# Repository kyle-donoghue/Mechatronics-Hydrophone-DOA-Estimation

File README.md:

# Mechatronics-Hydrophone-DOA-Estimation
 My work with using passive hydrophones to estimate the direction of arrival of an underwater acoustic ping. This project was made for SDSU's Mechatronics team for deployment on an autonomous submarine competition.

# How It Works
2 passive Aquarius hydrophones are connected to an op-amp network for amplification that is conneected to an Analog Digilent Discovery 2. The ADD2 is used as an ADC with their provided SDK. Python is then used for real-time capturing and processing of hydrophone data using threaded workloads and queues to send data between the workloads. Data is captured at 500kS/s at 12-bits continuously with a 1 second buffer on the recording thread and then is sent to the processing thread.

The processing thread then uses a 127-order bandpass filter from 20k-40kHz. Then, an energy vs. time signal is made in that frequency spectrum to see where in the buffer the spike of the acoustic ping is. Once the spike is located, the first couple of periods of it is taken and used for direction-of-arrival estimation. Next, the STFT is taken of the signal and a new signal is made up of the peaks of every FT in the series. This new complex signal has all the data we need for DOA estimation due to its time relative information on phase differences of the two hydrophones.

Now, Burg's Maximum Entropy Method is used on this new complex signal to calculate the power at each possible degree to make a power vs. degree signal. Finally, the peaks of this signal are found and their indices in the array correspond to the DOA. Finally, the first peak's index is is sent out to the main computer for use in autonomous direction.

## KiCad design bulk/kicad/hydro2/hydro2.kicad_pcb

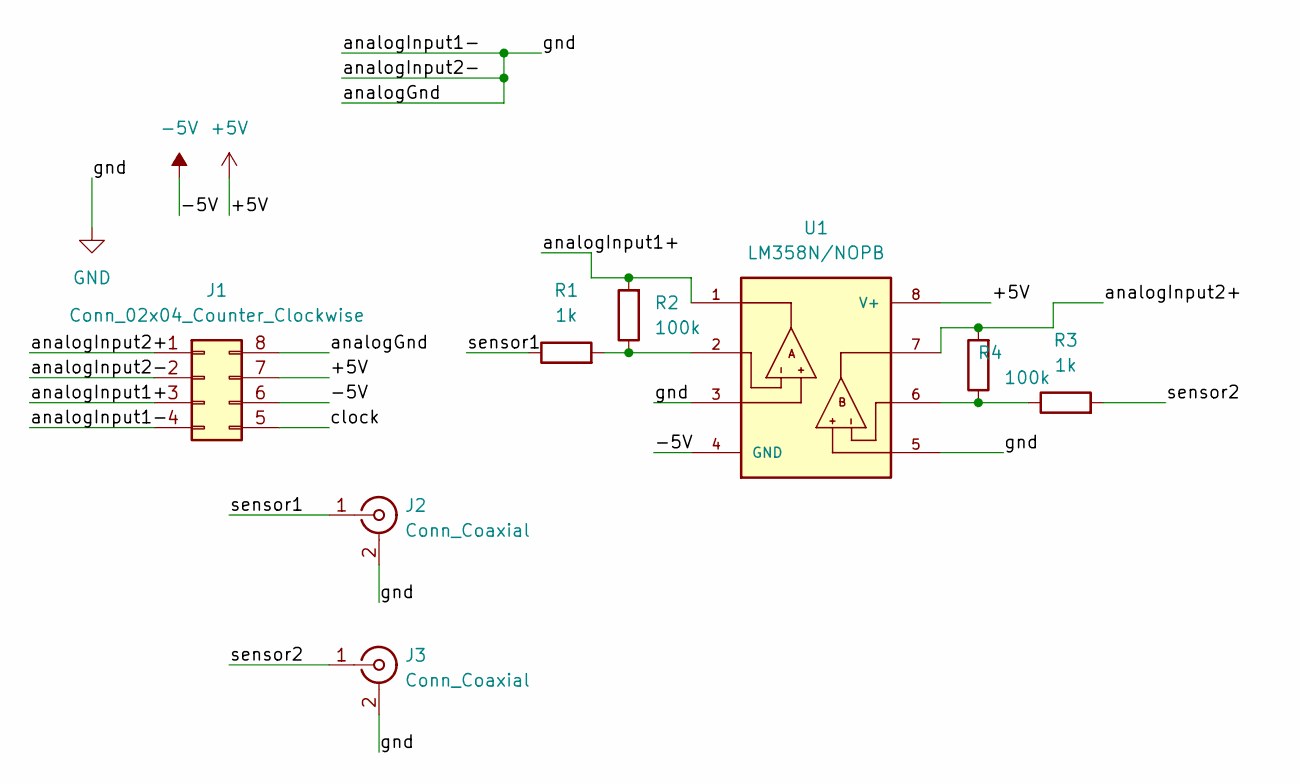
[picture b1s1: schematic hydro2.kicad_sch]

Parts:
J1: Conn_02x04_Counter_Clockwise; PinHeader_2x04_P2.54mm_Vertical
J2, J3: Conn_Coaxial; BNC_TEConnectivity_1478204_Vertical
R1, R3: 1k; R_Axial_DIN0207_L6.3mm_D2.5mm_P10.16mm_Horizontal
R2, R4: 100k; R_Axial_DIN0207_L6.3mm_D2.5mm_P10.16mm_Horizontal
U1: LM358N/NOPB; DIP794W45P254L959H508Q8

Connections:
+5V: J1.7, U1.8 (V+)
-5V: J1.6, U1.4 (GND)
/analogInput1+: J1.3, R2.2, U1.1
/analogInput2+: J1.1, R4.2, U1.7
/clock: J1.5
/sensor1: J2.1 (In), R1.1
/sensor2: J3.1 (In), R3.2
GND: J1.2, J1.4, J1.8, J2.2 (Ext), J3.2 (Ext), U1.3, U1.5
unnamed: R1.2, R2.1, U1.2
unnamed: R3.1, R4.1, U1.6

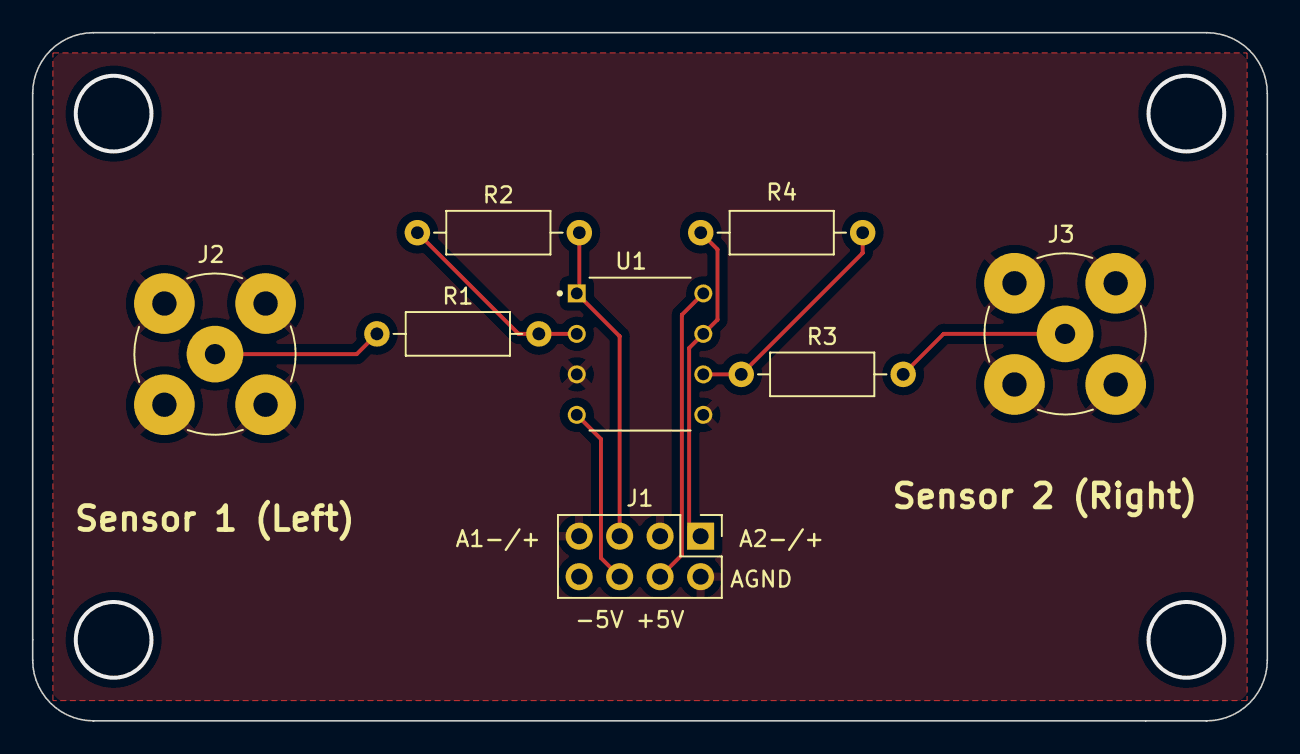
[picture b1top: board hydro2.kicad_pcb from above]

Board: 2 copper layers, 77.5 x 43.2 mm, 8 parts (0 on the bottom side), 9 nets.

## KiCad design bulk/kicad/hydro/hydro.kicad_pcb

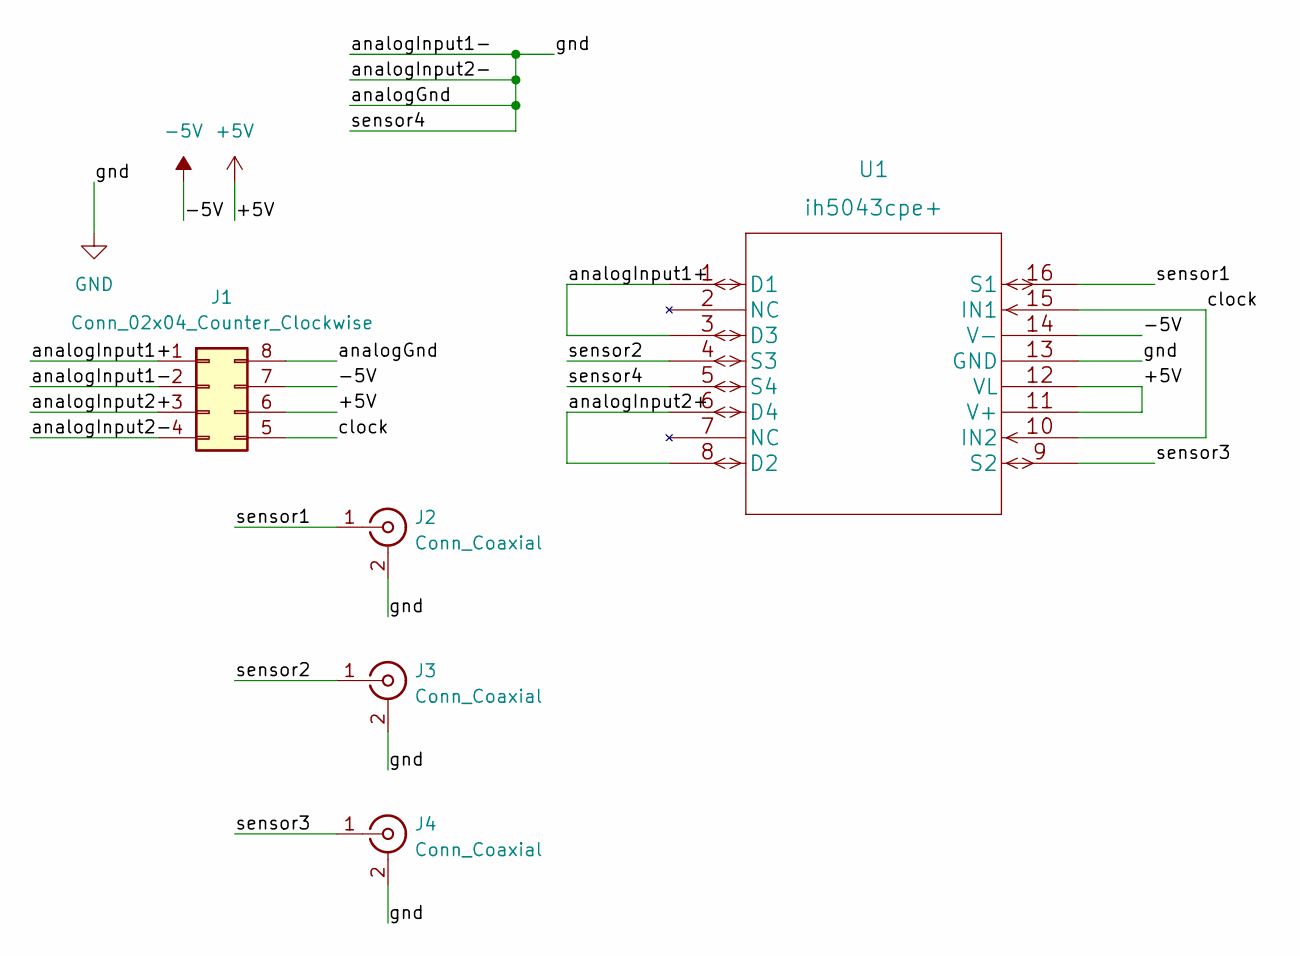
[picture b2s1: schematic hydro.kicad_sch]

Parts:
J1: Conn_02x04_Counter_Clockwise; PinHeader_2x04_P2.54mm_Vertical
J2, J3, J4: Conn_Coaxial; BNC_TEConnectivity_1478204_Vertical
U1: ih5043cpe+; ih5043cpe&plus_

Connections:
+5V: J1.6, U1.11 (V+), U1.12 (VL)
-5V: J1.7, U1.14 (V-)
/analogInput1+: J1.1, U1.1 (D1), U1.3 (D3)
/analogInput2+: J1.3, U1.6 (D4), U1.8 (D2)
/clock: J1.5, U1.10 (IN2), U1.15 (IN1)
/sensor1: J2.1 (In), U1.16 (S1)
/sensor2: J3.1 (In), U1.4 (S3)
/sensor3: J4.1 (In), U1.9 (S2)
GND: J1.2, J1.4, J1.8, J2.2 (Ext), J3.2 (Ext), J4.2 (Ext), U1.5 (S4), U1.13 (GND)

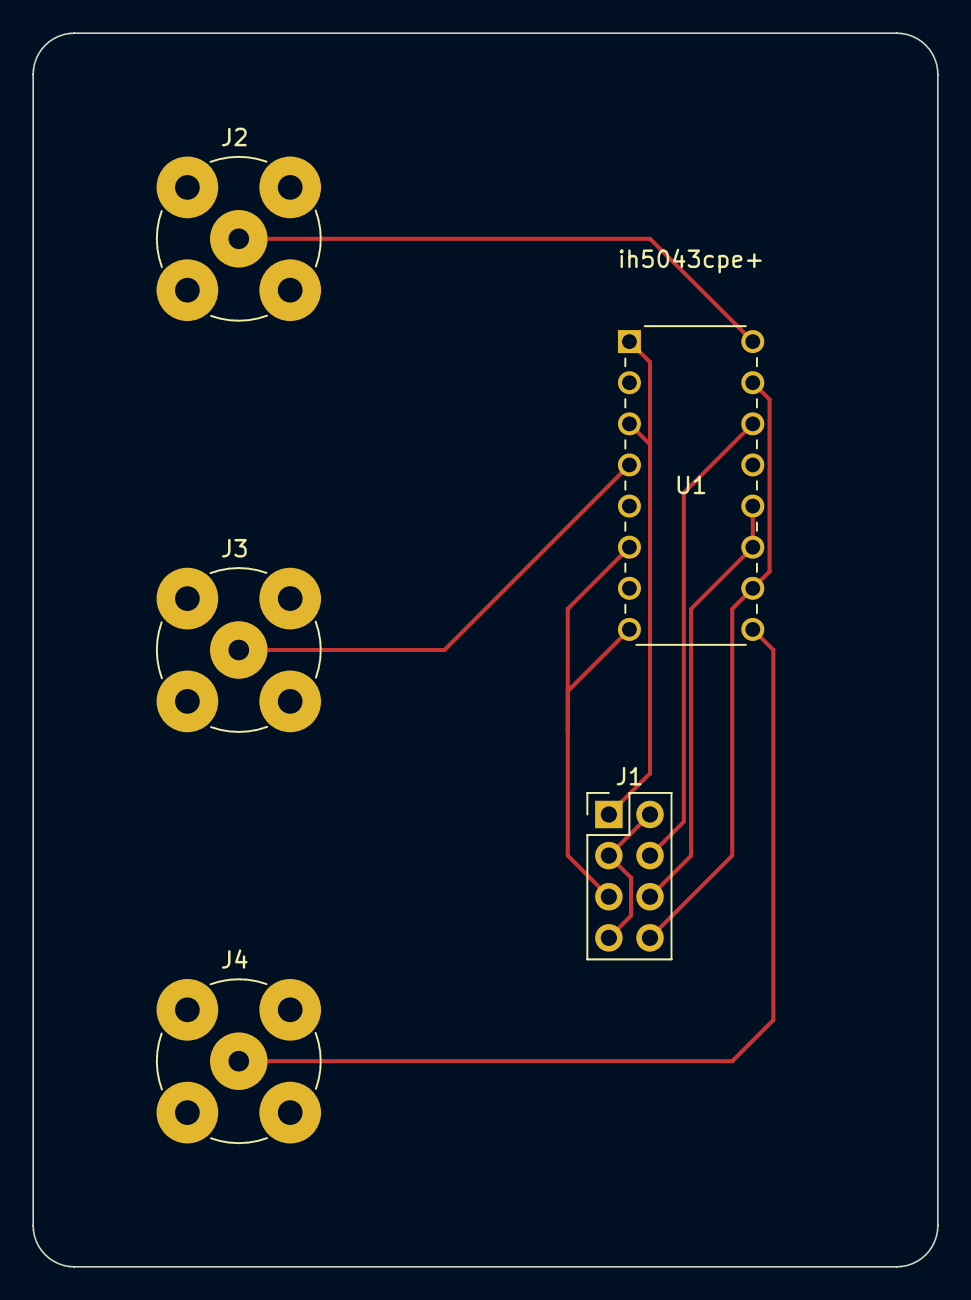
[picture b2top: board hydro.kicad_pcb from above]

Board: 2 copper layers, 55.9 x 76.2 mm, 5 parts (0 on the bottom side), 9 nets.
